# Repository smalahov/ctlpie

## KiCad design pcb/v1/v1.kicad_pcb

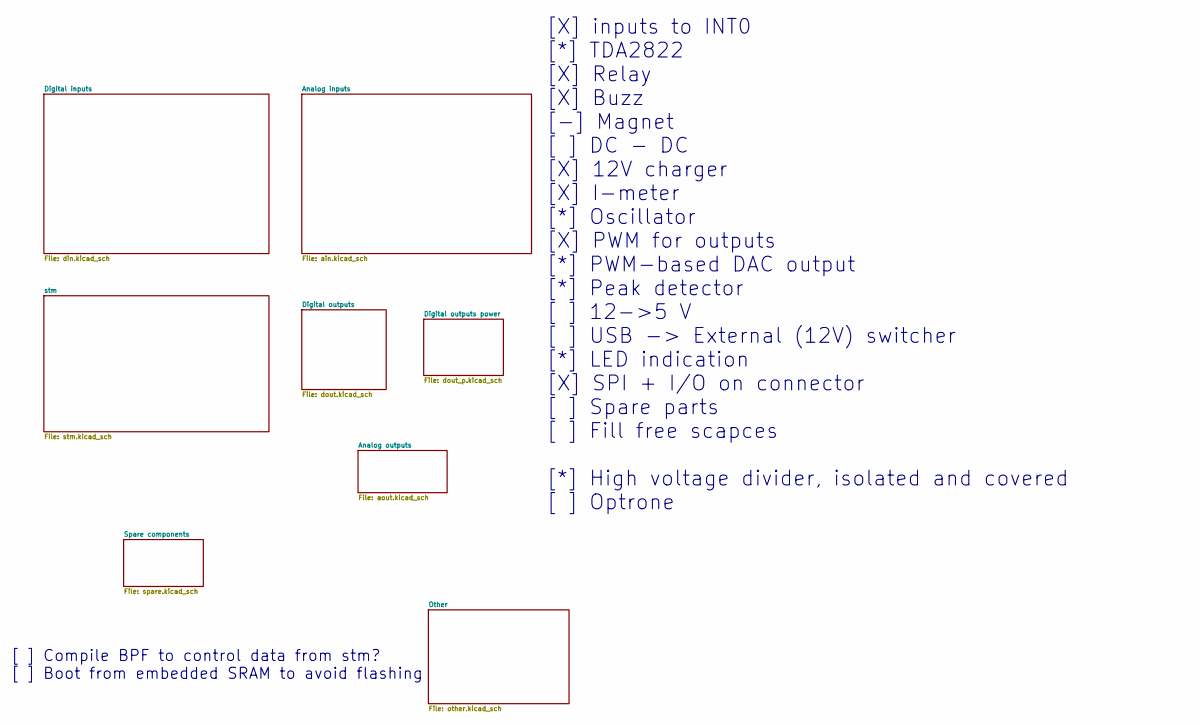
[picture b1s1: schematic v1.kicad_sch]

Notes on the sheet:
[X] inputs to INT0 [*] TDA2822 [X] Relay [X] Buzz [-] Magnet [ ] DC - DC [X] 12V charger [X] I-meter [*] Oscillator [X] PWM for outputs [*] PWM-based DAC output [*] Peak detector [ ] 12->5 V [ ] USB -> External (12V) switcher [*] LED indication [X] SPI + I/O on connector [ ] Spare parts [ ] Fill fr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
[ ] Compile BPF to control data from stm? [ ] Boot from embedded SRAM to avoid flashing

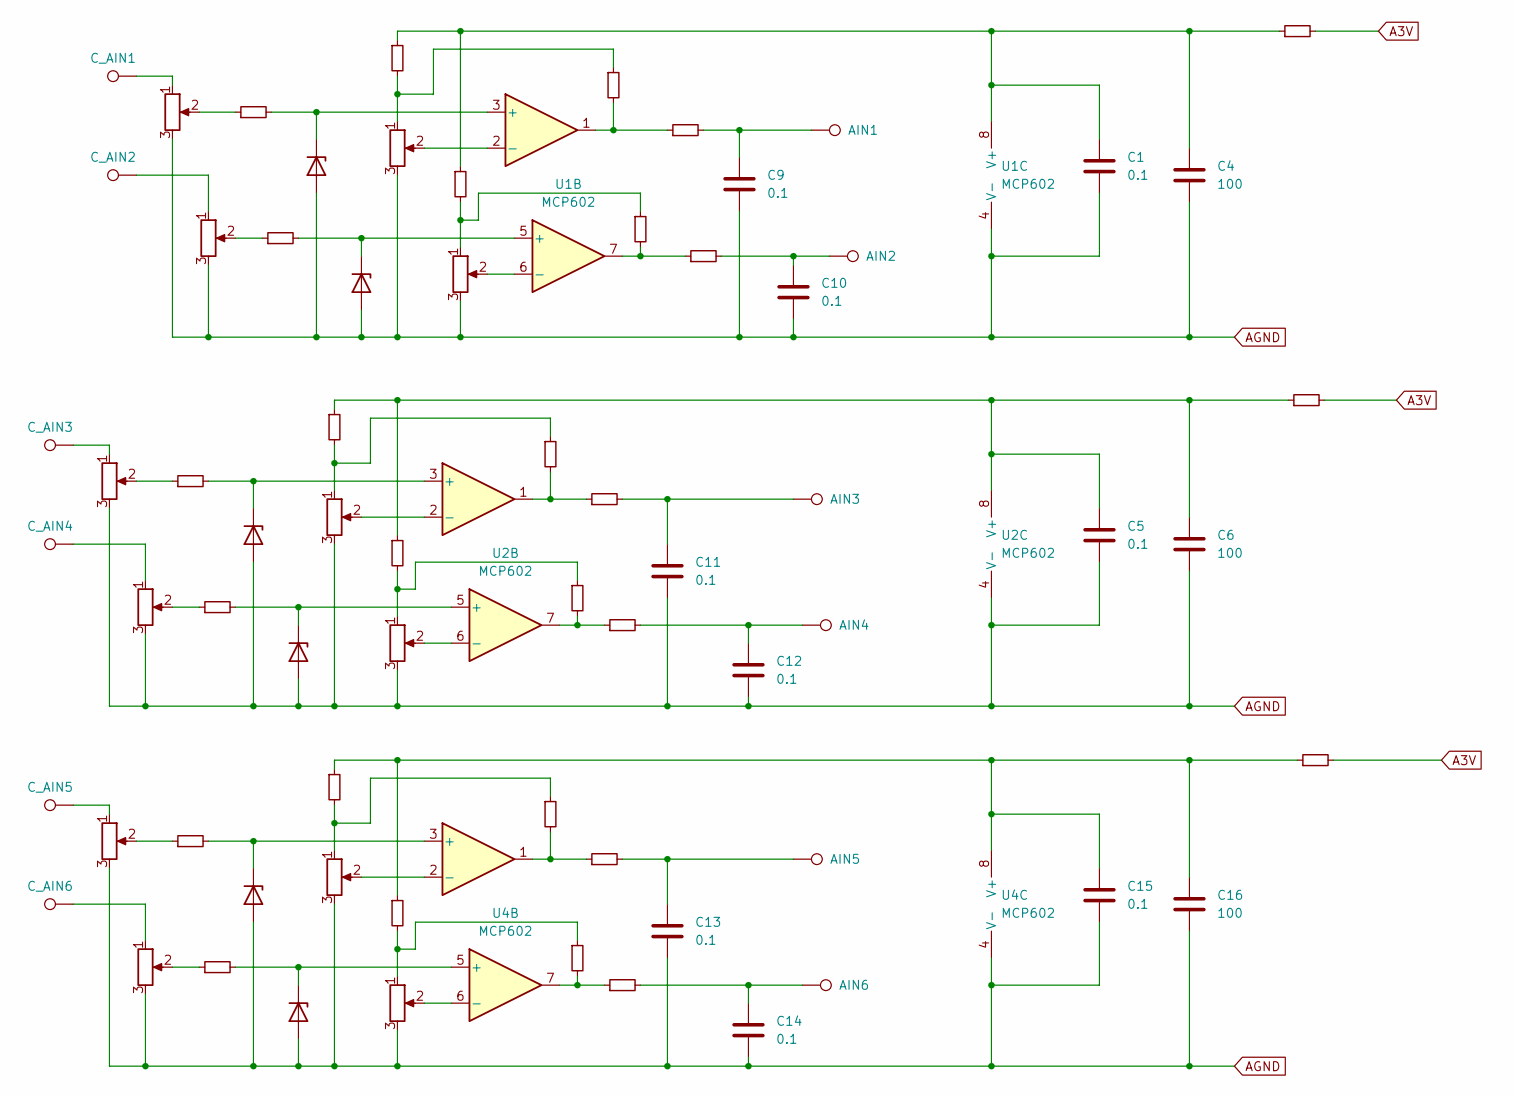
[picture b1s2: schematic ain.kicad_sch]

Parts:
AIN1, AIN2, AIN3, AIN4, AIN5, AIN6: TestPoint; TestPoint_Pad_2.0x2.0mm
C1, C5, C9, C10, C11, C12, C13, C14, C15: 0.1; C_1206_3216Metric
C4, C6, C16: 100; C_1206_3216Metric
C_AIN1, C_AIN2, C_AIN3, C_AIN4, C_AIN5, C_AIN6: TestPoint; TestPoint_Pad_D2.0mm
D2, D3, D9, D10, D11, D12: D_Zener; D_SOD-123
J1, J2, J3, J4, J5, J6, J7, J8, J9, J10, J11, J12, J13, J14, J15, J16, J18, J19, J20: R_Small; R_1206_3216Metric_Pad1.30x1.75mm_HandSolder
R5, R6, R50, R51, R52, R53, R200, R201: R_Small; R_1206_3216Metric_Pad1.30x1.75mm_HandSolder
RV1, RV2, RV3, RV4, RV5, RV6, RV7, RV8, RV9, RV10, RV14, RV15: R_Potentiometer; Potentiometer_Bourns_TC33X_Vertical
U1, U2, U4: MCP602; SOIC-8_3.9x4.9mm_P1.27mm

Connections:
A3V: J18.2, J19.2, J20.2; also elsewhere on the board
AGND: C1.2, C4.2, C5.2, C6.2, C9.2, C10.2, C11.2, C12.2, C13.2, C14.2, C15.2, C16.2, D2.2 (A), D3.2 (A), D9.2 (A), D10.2 (A), D11.2 (A), D12.2 (A), RV1.3, RV2.3, RV3.3, RV4.3, RV5.3, RV6.3, RV7.3, RV8.3, RV9.3, RV10.3, RV14.3, RV15.3, U1.4 (V-), U2.4 (V-), U4.4 (V-); also elsewhere on the board
unnamed 8: AIN1.1, C9.1, R200.2; also elsewhere on the board
unnamed 9: AIN2.1, C10.1, R201.2; also elsewhere on the board
unnamed 10: AIN3.1, C11.1, J9.2; also elsewhere on the board
unnamed 11: AIN4.1, C12.1, J10.2; also elsewhere on the board
unnamed 12: AIN5.1, C13.1, J15.2; also elsewhere on the board
unnamed 13: AIN6.1, C14.1, J16.2; also elsewhere on the board
unnamed: C_AIN1.1, RV1.1
unnamed: C_AIN2.1, RV5.1
unnamed: C_AIN3.1, RV3.1
unnamed: C_AIN4.1, RV7.1
unnamed: C_AIN5.1, RV9.1
unnamed: C_AIN6.1, RV10.1
unnamed: D2.1 (K), R5.2, U1.3 (+)
unnamed: D3.1 (K), R6.2, U1.5 (+)
unnamed: D9.1 (K), R50.2, U2.3 (+)
unnamed: D10.1 (K), R51.2, U2.5 (+)
unnamed: D11.1 (K), R52.2, U4.3 (+)
unnamed: D12.1 (K), R53.2, U4.5 (+)
unnamed: J1.2, J2.1, RV2.1
unnamed: J2.2, R200.1, U1.1
unnamed: J3.2, J4.1, RV6.1
unnamed: J4.2, R201.1, U1.7
unnamed: J5.2, J7.1, RV4.1
unnamed: J6.2, J8.1, RV8.1
unnamed: J7.2, J9.1, U2.1
unnamed: J8.2, J10.1, U2.7
unnamed: J11.2, J13.1, RV14.1
unnamed: J12.2, J14.1, RV15.1
unnamed: J13.2, J15.1, U4.1
unnamed: J14.2, J16.1, U4.7
unnamed: R5.1, RV1.2
unnamed: R6.1, RV5.2
unnamed: R50.1, RV3.2
unnamed: R51.1, RV7.2
unnamed: R52.1, RV9.2
unnamed: R53.1, RV10.2
unnamed: RV2.2, U1.2 (-)
unnamed: RV6.2, U1.6 (-)
unnamed: C1.1, C4.1, J1.1, J3.1, J18.1, U1.8 (V+)
unnamed: RV4.2, U2.2 (-)
unnamed: RV8.2, U2.6 (-)
unnamed: C5.1, C6.1, J5.1, J6.1, J19.1, U2.8 (V+)
unnamed: RV14.2, U4.2 (-)
unnamed: RV15.2, U4.6 (-)
unnamed: C15.1, C16.1, J11.1, J12.1, J20.1, U4.8 (V+)

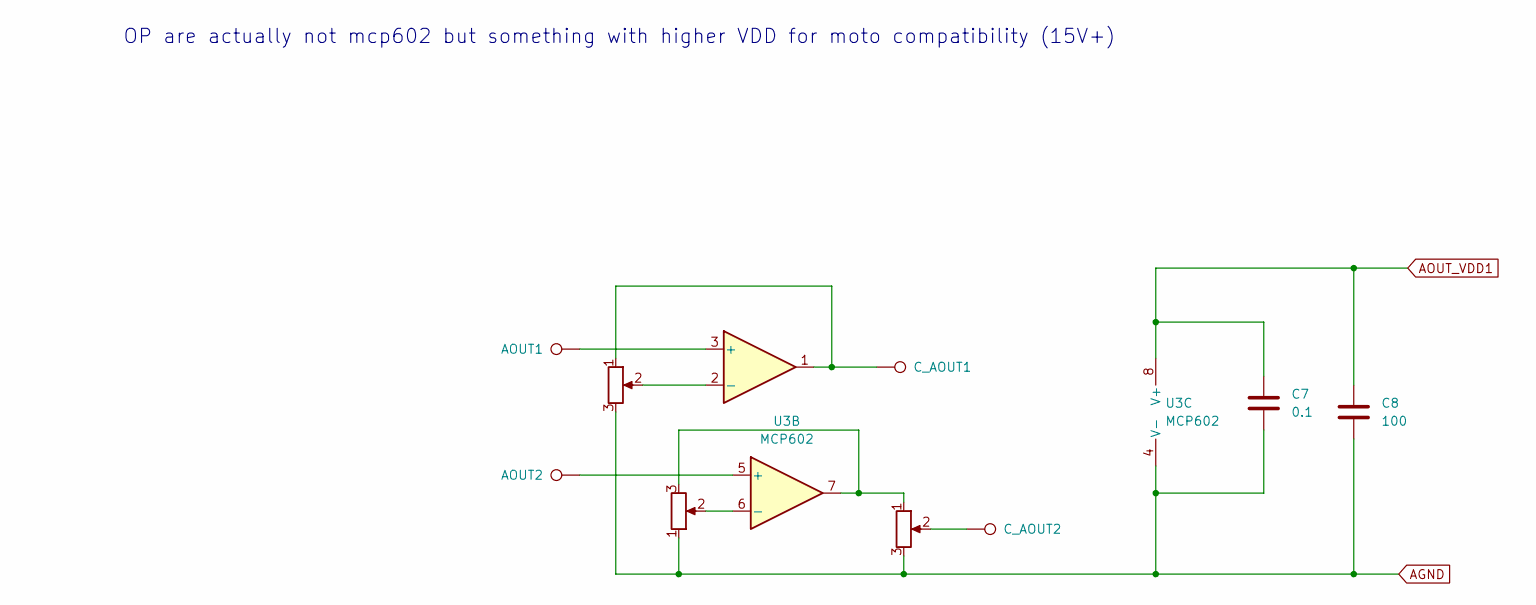
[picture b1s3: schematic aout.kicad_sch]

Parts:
AOUT1, AOUT2: TestPoint; TestPoint_Pad_2.0x2.0mm
C7: 0.1; C_1206_3216Metric
C8: 100; C_1206_3216Metric
C_AOUT1, C_AOUT2: TestPoint; TestPoint_Pad_D2.0mm
RV11, RV12, RV13: R_Potentiometer; Potentiometer_Bourns_TC33X_Vertical
U3: MCP602; SOIC-8_3.9x4.9mm_P1.27mm

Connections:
AGND: C7.2, C8.2, RV11.3, RV12.1, RV13.3, U3.4 (V-); also elsewhere on the board
AOUT_VDD1: C7.1, C8.1, U3.8 (V+)
unnamed: C_AOUT1.1, RV11.1, U3.1
unnamed: C_AOUT2.1, RV13.2
unnamed: RV12.3, RV13.1, U3.7
unnamed: AOUT1.1, U3.3 (+)
unnamed: RV11.2, U3.2 (-)
unnamed: AOUT2.1, U3.5 (+)
unnamed: RV12.2, U3.6 (-)

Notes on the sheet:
OP are actually not mcp602 but something with higher VDD for moto compatibility (15V+)

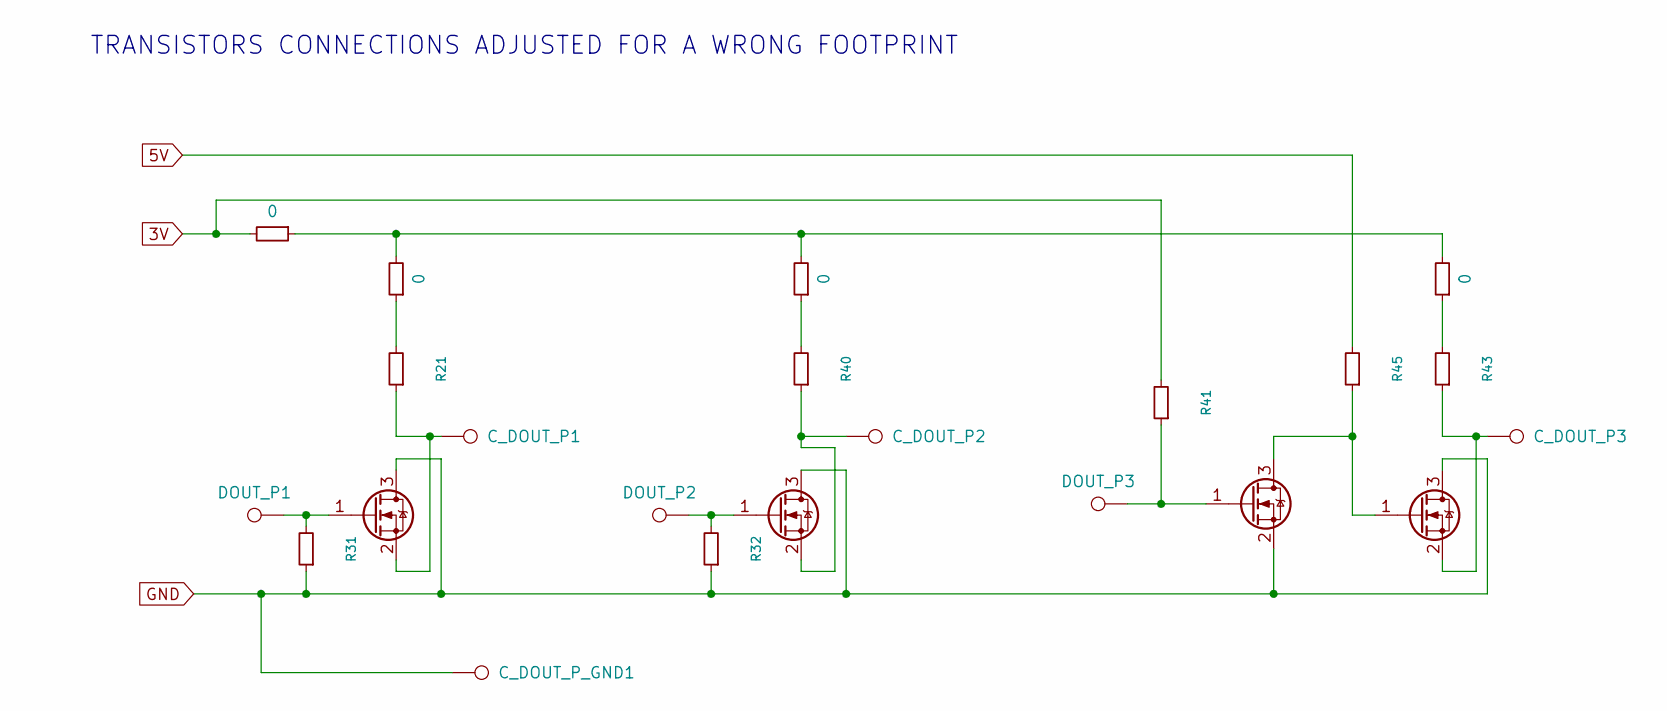
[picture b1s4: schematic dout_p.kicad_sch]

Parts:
C_DOUT_P1, C_DOUT_P2, C_DOUT_P3: TestPoint; TestPoint_Pad_D2.0mm
C_DOUT_P_GND1: TestPoint; TestPoint_Pad_D2.0mm
DOUT_P1, DOUT_P2, DOUT_P3: TestPoint; TestPoint_Pad_2.0x2.0mm
Q6, Q12, Q13: 35N06; TO-252-2
Q14: 2N7002K; SOT-23-3
R21, R31, R32, R40, R41, R43, R45: R_Small; R_1206_3216Metric_Pad1.30x1.75mm_HandSolder
R22, R37, R42, R44: 0; R_1206_3216Metric_Pad1.30x1.75mm_HandSolder

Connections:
3V: R41.2, R44.2; also elsewhere on the board
5V: R45.2; also elsewhere on the board
GND: C_DOUT_P_GND1.1, Q6.3 (D), Q12.3 (D), Q13.3 (D), Q14.2 (S), R31.1, R32.1; also elsewhere on the board
unnamed: DOUT_P1.1, Q6.1 (G), R31.2
unnamed: C_DOUT_P1.1, Q6.2 (S), R21.1
unnamed: DOUT_P2.1, Q12.1 (G), R32.2
unnamed: C_DOUT_P2.1, Q12.2 (S), R40.1
unnamed: Q13.1 (G), Q14.3 (D), R45.1
unnamed: C_DOUT_P3.1, Q13.2 (S), R43.1
unnamed: DOUT_P3.1, Q14.1 (G), R41.1
unnamed: R21.2, R22.1
unnamed: R22.2, R37.2, R42.2, R44.1
unnamed: R37.1, R40.2
unnamed: R42.1, R43.2

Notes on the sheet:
TRANSISTORS CONNECTIONS ADJUSTED FOR A WRONG FOOTPRINT

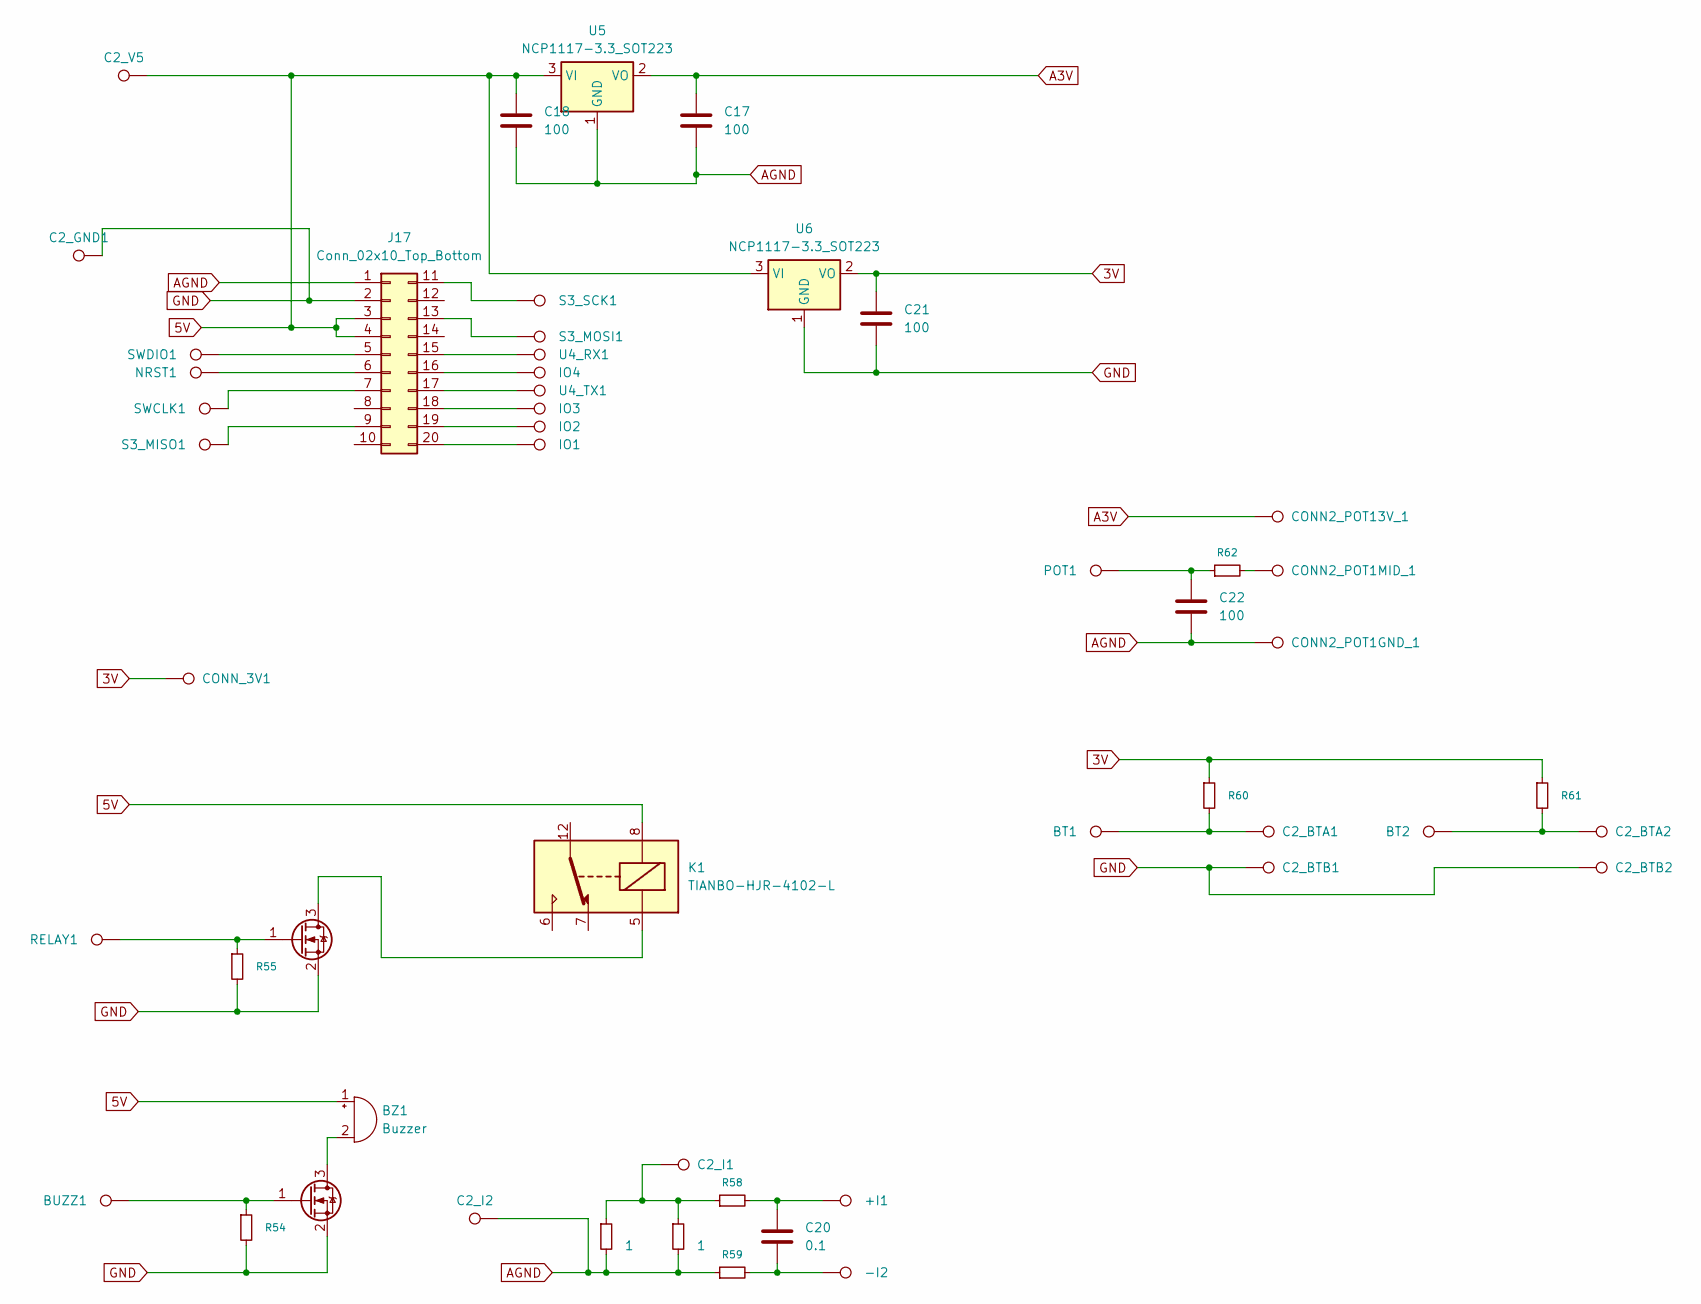
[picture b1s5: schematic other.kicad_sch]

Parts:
+I1: TestPoint; TestPoint_Pad_2.0x2.0mm
-I2: TestPoint; TestPoint_Pad_2.0x2.0mm
BT1, BT2: TestPoint; TestPoint_Pad_2.0x2.0mm
BUZZ1: TestPoint; TestPoint_Pad_2.0x2.0mm
BZ1: Buzzer; Indicator_PUI_AI-1440-TWT-24V-2-R
C2_BTA1, C2_BTA2, C2_BTB1, C2_BTB2, C2_GND1, C2_I1, C2_I2, C2_V5: TestPoint; TestPoint_Pad_D2.0mm
C17, C18, C21, C22: 100; C_1206_3216Metric
C20: 0.1; C_1206_3216Metric
CONN2_POT1GND_1, CONN2_POT1MID_1, CONN2_POT13V_1: TestPoint; TestPoint_Pad_D2.0mm
CONN_3V1: TestPoint; TestPoint_Pad_D2.0mm
IO1, IO2, IO3, IO4: TestPoint; TestPoint_Pad_2.0x2.0mm
J17: Conn_02x10_Top_Bottom; IDC-Header_2x10_P2.54mm_Vertical
K1: TIANBO-HJR-4102-L; Relay_SPDT_HJR-4102
NRST1: TestPoint; TestPoint_Pad_2.0x2.0mm
POT1: TestPoint; TestPoint_Pad_2.0x2.0mm
Q17, Q18: 2N7002K; SOT-23-3
R54, R55, R58, R59, R60, R61, R62: R_Small; R_1206_3216Metric_Pad1.30x1.75mm_HandSolder
R56, R57: 1; R_2512_6332Metric_Pad1.40x3.35mm_HandSolder
RELAY1: TestPoint; TestPoint_Pad_2.0x2.0mm
S3_MISO1, S3_MOSI1, S3_SCK1: TestPoint; TestPoint_Pad_2.0x2.0mm
SWCLK1: TestPoint; TestPoint_Pad_2.0x2.0mm
SWDIO1: TestPoint; TestPoint_Pad_2.0x2.0mm
U4_RX1, U4_TX1: TestPoint; TestPoint_Pad_2.0x2.0mm
U5, U6: NCP1117-3.3_SOT223; SOT-223-3_TabPin2

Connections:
3V: C21.1, CONN_3V1.1, R60.1, R61.1, U6.2 (VO); also elsewhere on the board
5V: BZ1.1 (+), C2_V5.1, C18.1, J17.3, J17.4, K1.8, U5.3 (VI), U6.3 (VI); also elsewhere on the board
A3V: C17.1, CONN2_POT13V_1.1, U5.2 (VO); also elsewhere on the board
AGND: C2_I2.1, C17.2, C18.2, C22.2, CONN2_POT1GND_1.1, J17.1, R56.2, R57.2, R59.1, U5.1 (GND); also elsewhere on the board
GND: C2_BTB1.1, C2_BTB2.1, C2_GND1.1, C21.2, J17.2, Q17.2 (S), Q18.2 (S), R54.2, R55.2, U6.1 (GND); also elsewhere on the board
unnamed 6: +I1.1, C20.1, R58.2; also elsewhere on the board
unnamed 7: -I2.1, C20.2, R59.2; also elsewhere on the board
unnamed: BT1.1, C2_BTA1.1, R60.2
unnamed: BT2.1, C2_BTA2.1, R61.2
unnamed: BZ1.2 (-), Q17.3 (D)
unnamed: C2_I1.1, R56.1, R57.1, R58.1
unnamed 18: C22.1, POT1.1, R62.1; also elsewhere on the board
unnamed: CONN2_POT1MID_1.1, R62.2
unnamed: J17.5, SWDIO1.1
unnamed 75: J17.6, NRST1.1; also elsewhere on the board
unnamed: J17.7, SWCLK1.1
unnamed: J17.9, S3_MISO1.1
unnamed: J17.11, S3_SCK1.1
unnamed: J17.13, S3_MOSI1.1
unnamed: J17.15, U4_RX1.1
unnamed: IO4.1, J17.16
unnamed: J17.17, U4_TX1.1
unnamed: IO3.1, J17.18
unnamed: IO2.1, J17.19
unnamed: IO1.1, J17.20
unnamed: BUZZ1.1, Q17.1 (G), R54.1
unnamed: K1.5, Q18.3 (D)
unnamed: Q18.1 (G), R55.1, RELAY1.1

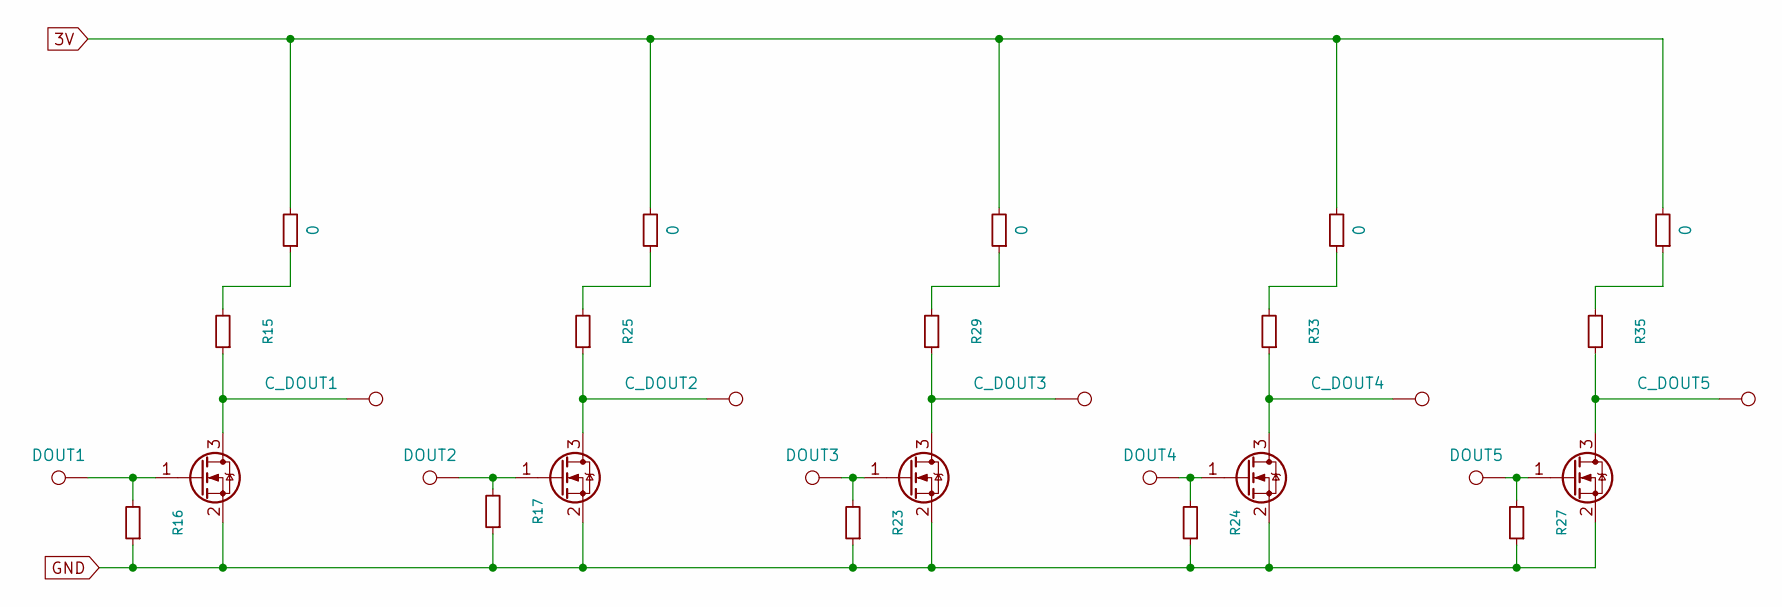
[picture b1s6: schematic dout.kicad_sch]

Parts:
C_DOUT1, C_DOUT2, C_DOUT3, C_DOUT4, C_DOUT5: TestPoint; TestPoint_Pad_D2.0mm
DOUT1, DOUT2, DOUT3, DOUT4, DOUT5: TestPoint; TestPoint_Pad_2.0x2.0mm
Q5, Q7, Q8, Q9, Q10: 2N7002K; SOT-23-3
R15, R16, R17, R23, R24, R25, R27, R29, R33, R35: R_Small; R_1206_3216Metric_Pad1.30x1.75mm_HandSolder
R18, R26, R30, R34, R36: 0; R_1206_3216Metric_Pad1.30x1.75mm_HandSolder

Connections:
3V: R18.2, R26.2, R30.2, R34.2, R36.2; also elsewhere on the board
GND: Q5.2 (S), Q7.2 (S), Q8.2 (S), Q9.2 (S), Q10.2 (S), R16.1, R17.1, R23.1, R24.1, R27.1; also elsewhere on the board
unnamed: C_DOUT1.1, Q5.3 (D), R15.1
unnamed: DOUT1.1, Q5.1 (G), R16.2
unnamed: C_DOUT2.1, Q7.3 (D), R25.1
unnamed: DOUT2.1, Q7.1 (G), R17.2
unnamed: C_DOUT3.1, Q8.3 (D), R29.1
unnamed: DOUT3.1, Q8.1 (G), R23.2
unnamed: C_DOUT4.1, Q9.3 (D), R33.1
unnamed: DOUT4.1, Q9.1 (G), R24.2
unnamed: C_DOUT5.1, Q10.3 (D), R35.1
unnamed: DOUT5.1, Q10.1 (G), R27.2
unnamed: R15.2, R18.1
unnamed: R25.2, R26.1
unnamed: R29.2, R30.1
unnamed: R33.2, R34.1
unnamed: R35.2, R36.1

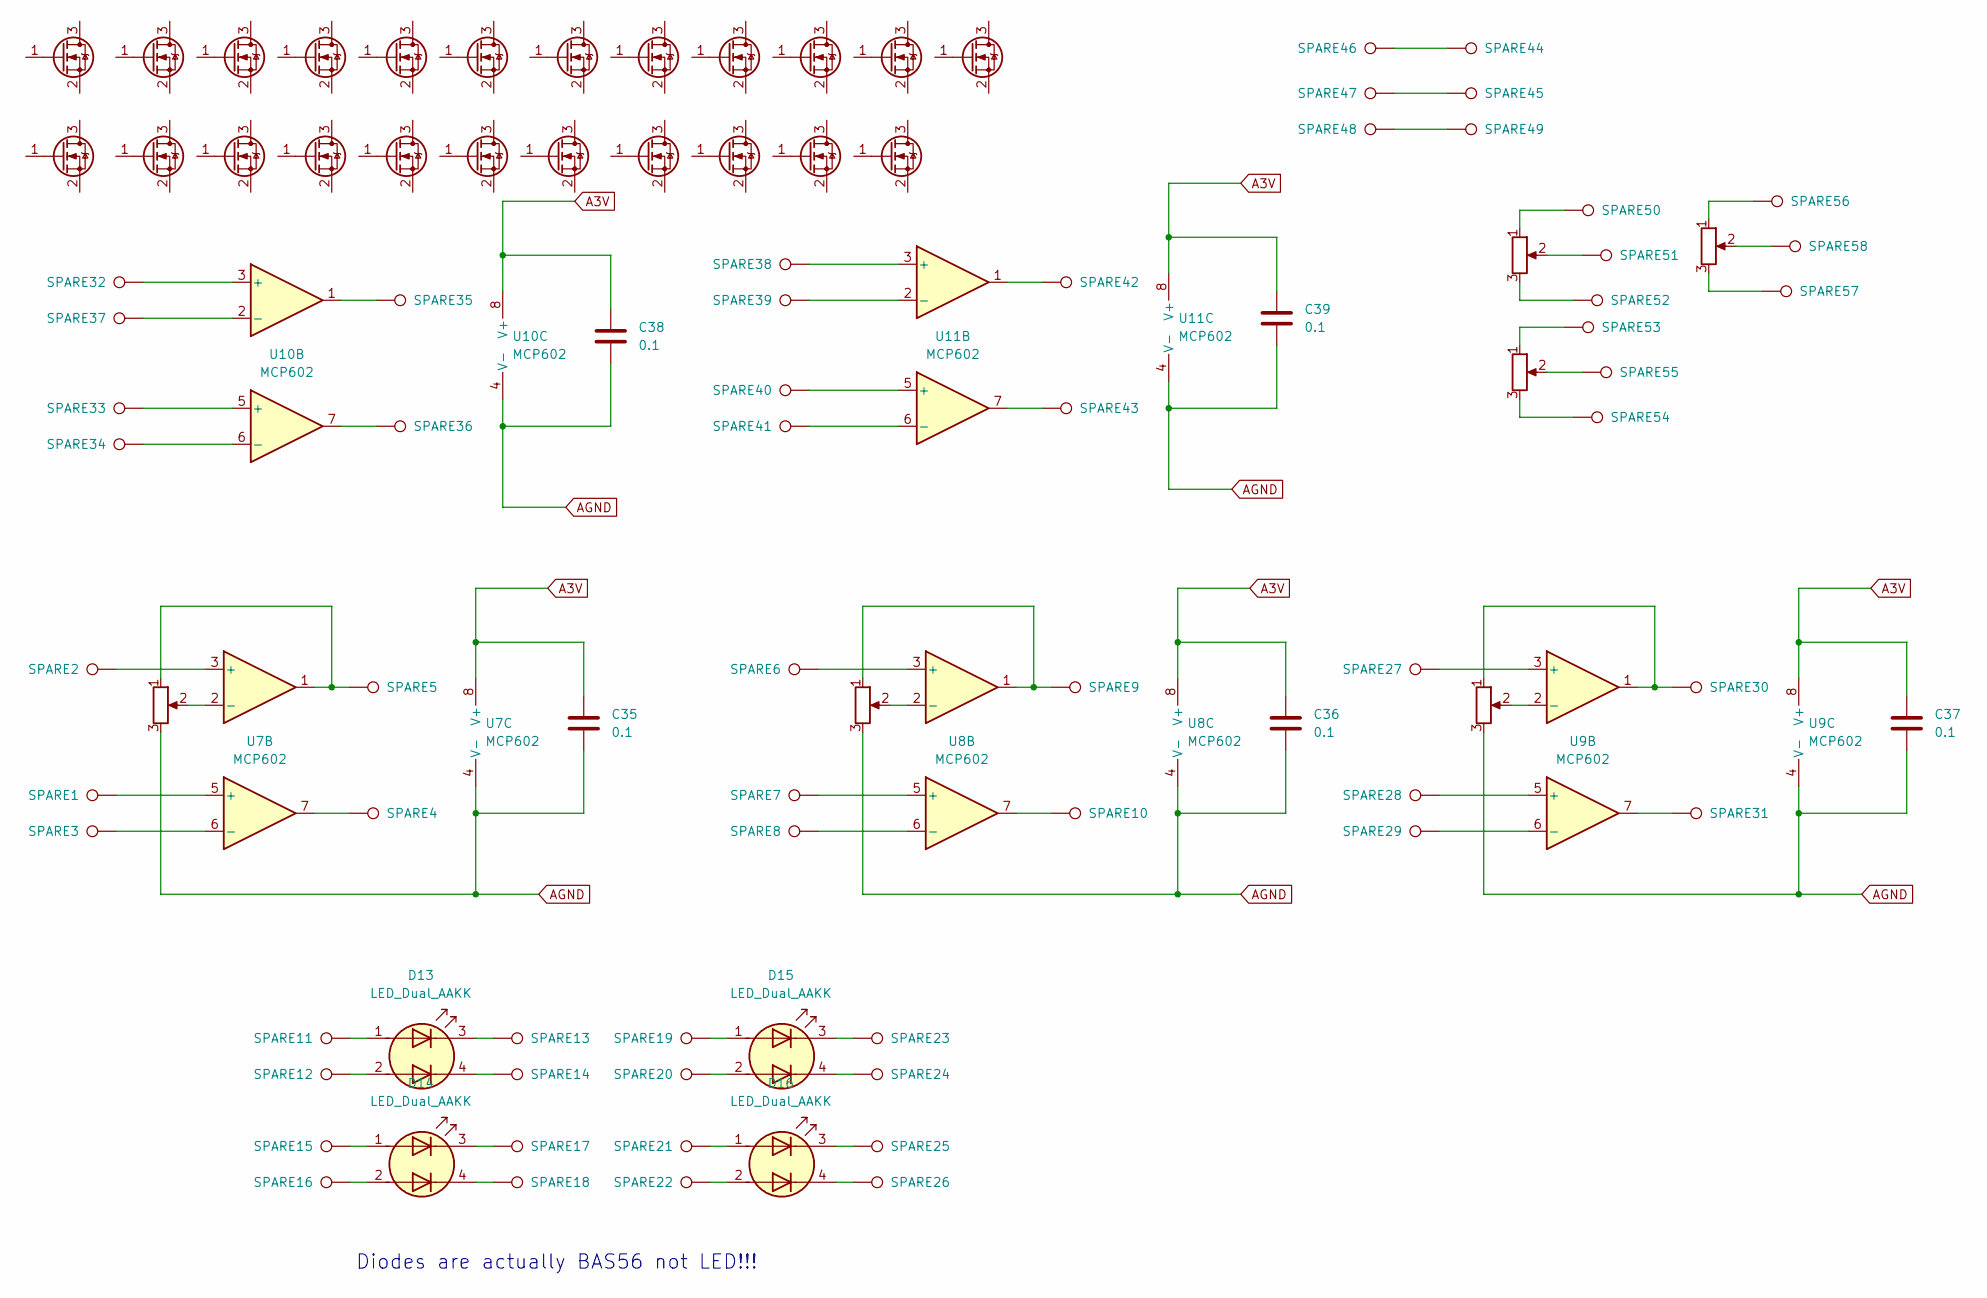
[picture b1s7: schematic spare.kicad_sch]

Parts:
C35, C36, C37, C38, C39: 0.1; C_1206_3216Metric
D13, D14, D15, D16: LED_Dual_AAKK; SOT-143
Q11, Q19, Q20, Q21, Q22, Q23, Q24, Q25, Q26, Q27, Q28, Q29, Q30, Q31, Q32, Q33, Q34, Q35, Q36, Q37, Q38, Q39, Q40: 2N7002K; SOT-23_Handsoldering
RV16, RV17, RV18, RV19, RV20, RV21: R_Potentiometer; Potentiometer_Bourns_TC33X_Vertical
SPARE1, SPARE2, SPARE3, SPARE4, SPARE5, SPARE6, SPARE7, SPARE8, SPARE9, SPARE10, SPARE11, SPARE12, SPARE13, SPARE14, SPARE15, SPARE16, SPARE17, SPARE18, SPARE19, SPARE20, SPARE21, SPARE22, SPARE23, SPARE24, SPARE25, SPARE26, SPARE27, SPARE28, SPARE29, SPARE30, SPARE31, SPARE32, SPARE33, SPARE34, SPARE35, SPARE36, SPARE37, SPARE38, SPARE39, SPARE40, SPARE41, SPARE42, SPARE43: TestPoint; TestPoint_Pad_1.0x1.0mm
SPARE44, SPARE45, SPARE49: TestPoint; TestPoint_Pad_D2.0mm
SPARE46, SPARE47, SPARE48: TestPoint; TestPoint_Pad_2.0x2.0mm
SPARE50, SPARE51, SPARE52, SPARE53, SPARE54, SPARE55, SPARE56, SPARE57, SPARE58: TestPoint; TestPoint_Pad_1.5x1.5mm
U7, U8, U9, U10, U11: MCP602; SOIC-8_3.9x4.9mm_P1.27mm

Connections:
A3V: C35.1, C36.1, C37.1, C38.1, C39.1, U7.8 (V+), U8.8 (V+), U9.8 (V+), U10.8 (V+), U11.8 (V+); also elsewhere on the board
AGND: C35.2, C36.2, C37.2, C38.2, C39.2, RV16.3, RV17.3, RV18.3, U7.4 (V-), U8.4 (V-), U9.4 (V-), U10.4 (V-), U11.4 (V-); also elsewhere on the board
unnamed: D13.1 (A1), SPARE11.1
unnamed: D13.2 (A2), SPARE12.1
unnamed: D13.3 (K1), SPARE13.1
unnamed: D13.4 (K2), SPARE14.1
unnamed: D14.1 (A1), SPARE15.1
unnamed: D14.2 (A2), SPARE16.1
unnamed: D14.3 (K1), SPARE17.1
unnamed: D14.4 (K2), SPARE18.1
unnamed: D15.1 (A1), SPARE19.1
unnamed: D15.2 (A2), SPARE20.1
unnamed: D15.3 (K1), SPARE23.1
unnamed: D15.4 (K2), SPARE24.1
unnamed: D16.1 (A1), SPARE21.1
unnamed: D16.2 (A2), SPARE22.1
unnamed: D16.3 (K1), SPARE25.1
unnamed: D16.4 (K2), SPARE26.1
unnamed: RV16.1, SPARE5.1, U7.1
unnamed: RV17.1, SPARE9.1, U8.1
unnamed: RV18.1, SPARE30.1, U9.1
unnamed: RV19.1, SPARE50.1
unnamed: RV19.2, SPARE51.1
unnamed: RV19.3, SPARE52.1
unnamed: RV20.1, SPARE53.1
unnamed: RV20.2, SPARE55.1
unnamed: RV20.3, SPARE54.1
unnamed: RV21.1, SPARE56.1
unnamed: RV21.2, SPARE58.1
unnamed: RV21.3, SPARE57.1
unnamed: SPARE4.1, U7.7
unnamed: SPARE10.1, U8.7
unnamed: SPARE31.1, U9.7
unnamed: SPARE35.1, U10.1
unnamed: SPARE36.1, U10.7
unnamed: SPARE42.1, U11.1
unnamed: SPARE43.1, U11.7
unnamed: SPARE44.1, SPARE46.1
unnamed: SPARE45.1, SPARE47.1
unnamed: SPARE48.1, SPARE49.1
unnamed: SPARE2.1, U7.3 (+)
unnamed: RV16.2, U7.2 (-)
unnamed: SPARE1.1, U7.5 (+)
unnamed: SPARE3.1, U7.6 (-)
unnamed: SPARE6.1, U8.3 (+)
unnamed: RV17.2, U8.2 (-)
unnamed: SPARE7.1, U8.5 (+)
unnamed: SPARE8.1, U8.6 (-)
unnamed: SPARE27.1, U9.3 (+)
unnamed: RV18.2, U9.2 (-)
unnamed: SPARE28.1, U9.5 (+)
unnamed: SPARE29.1, U9.6 (-)
unnamed: SPARE32.1, U10.3 (+)
unnamed: SPARE37.1, U10.2 (-)
unnamed: SPARE33.1, U10.5 (+)
unnamed: SPARE34.1, U10.6 (-)
unnamed: SPARE38.1, U11.3 (+)
unnamed: SPARE39.1, U11.2 (-)
unnamed: SPARE40.1, U11.5 (+)
unnamed: SPARE41.1, U11.6 (-)

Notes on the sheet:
Diodes are actually BAS56 not LED!!!

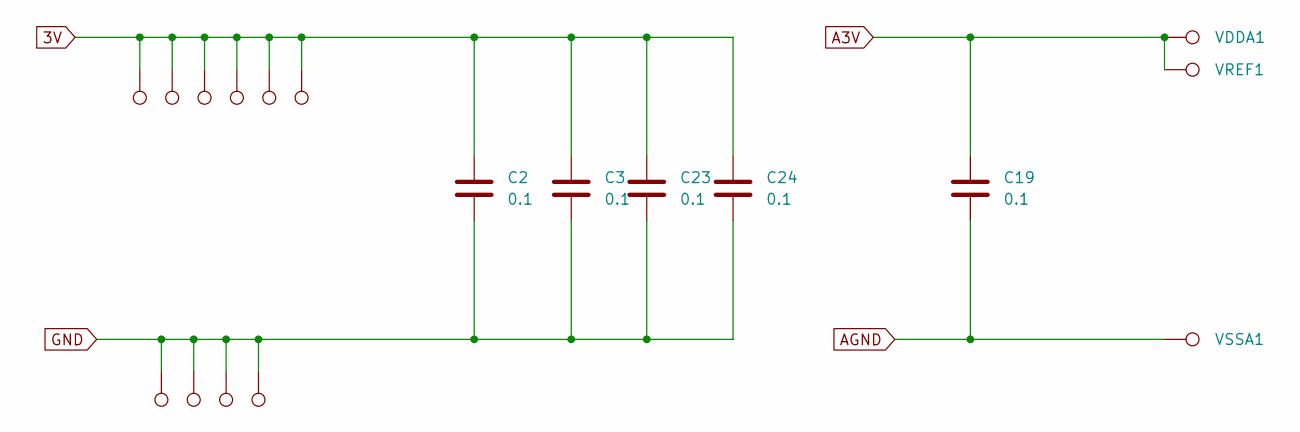
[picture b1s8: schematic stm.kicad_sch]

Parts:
C2, C3, C19, C23, C24: 0.1; C_1206_3216Metric
TP1, TP2, TP3, TP4, TP6, TP7, TP8, TP9, TP10, TP11: TestPoint; TestPoint_Pad_2.0x2.0mm
VDDA1: TestPoint; TestPoint_Pad_2.0x2.0mm
VREF1: TestPoint; TestPoint_Pad_2.0x2.0mm
VSSA1: TestPoint; TestPoint_Pad_2.0x2.0mm

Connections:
3V: C2.1, C3.1, C23.1, C24.1, TP6.1, TP7.1, TP8.1, TP9.1, TP10.1, TP11.1; also elsewhere on the board
A3V: C19.1, VDDA1.1, VREF1.1; also elsewhere on the board
AGND: C19.2, VSSA1.1; also elsewhere on the board
GND: C2.2, C3.2, C23.2, C24.2, TP1.1, TP2.1, TP3.1, TP4.1; also elsewhere on the board

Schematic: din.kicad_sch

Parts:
C_DIN1, C_DIN2, C_DIN3, C_DIN4, C_DIN5, C_DIN6: TestPoint; TestPoint_Pad_D2.0mm
D1, D4, D5, D6, D7, D8: D_Zener; D_SOD-123
DIN1, DIN2, DIN3, DIN4, DIN5, DIN6: TestPoint; TestPoint_Pad_2.0x2.0mm
Q1, Q2, Q3, Q4, Q15, Q16: 2N7002K; SOT-23-3
R1, R2, R3, R4, R7, R8, R9, R10, R11, R12, R13, R14, R19, R20, R46, R47, R48, R49: R_Small; R_1206_3216Metric_Pad1.30x1.75mm_HandSolder

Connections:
3V: R3.2, R8.2, R11.2, R14.2, R46.2, R49.2; also elsewhere on the board
GND: D1.2 (A), D4.2 (A), D5.2 (A), D6.2 (A), D7.2 (A), D8.2 (A), Q1.2 (S), Q2.2 (S), Q3.2 (S), Q4.2 (S), Q15.2 (S), Q16.2 (S), R1.2, R4.2, R9.2, R12.2, R19.2, R47.2; also elsewhere on the board
unnamed: C_DIN1.1, R1.1, R2.2
unnamed: C_DIN2.1, R4.1, R7.2
unnamed: C_DIN3.1, R9.1, R10.2
unnamed: C_DIN4.1, R12.1, R13.2
unnamed: C_DIN5.1, R19.1, R20.2
unnamed: C_DIN6.1, R47.1, R48.2
unnamed: D1.1 (K), Q1.1 (G), R2.1
unnamed: D4.1 (K), Q2.1 (G), R7.1
unnamed: D5.1 (K), Q3.1 (G), R10.1
unnamed: D6.1 (K), Q4.1 (G), R13.1
unnamed: D7.1 (K), Q15.1 (G), R20.1
unnamed: D8.1 (K), Q16.1 (G), R48.1
unnamed: DIN1.1, Q1.3 (D), R3.1
unnamed: DIN2.1, Q2.3 (D), R8.1
unnamed: DIN3.1, Q3.3 (D), R11.1
unnamed: DIN4.1, Q4.3 (D), R14.1
unnamed: DIN5.1, Q15.3 (D), R46.1
unnamed: DIN6.1, Q16.3 (D), R49.1

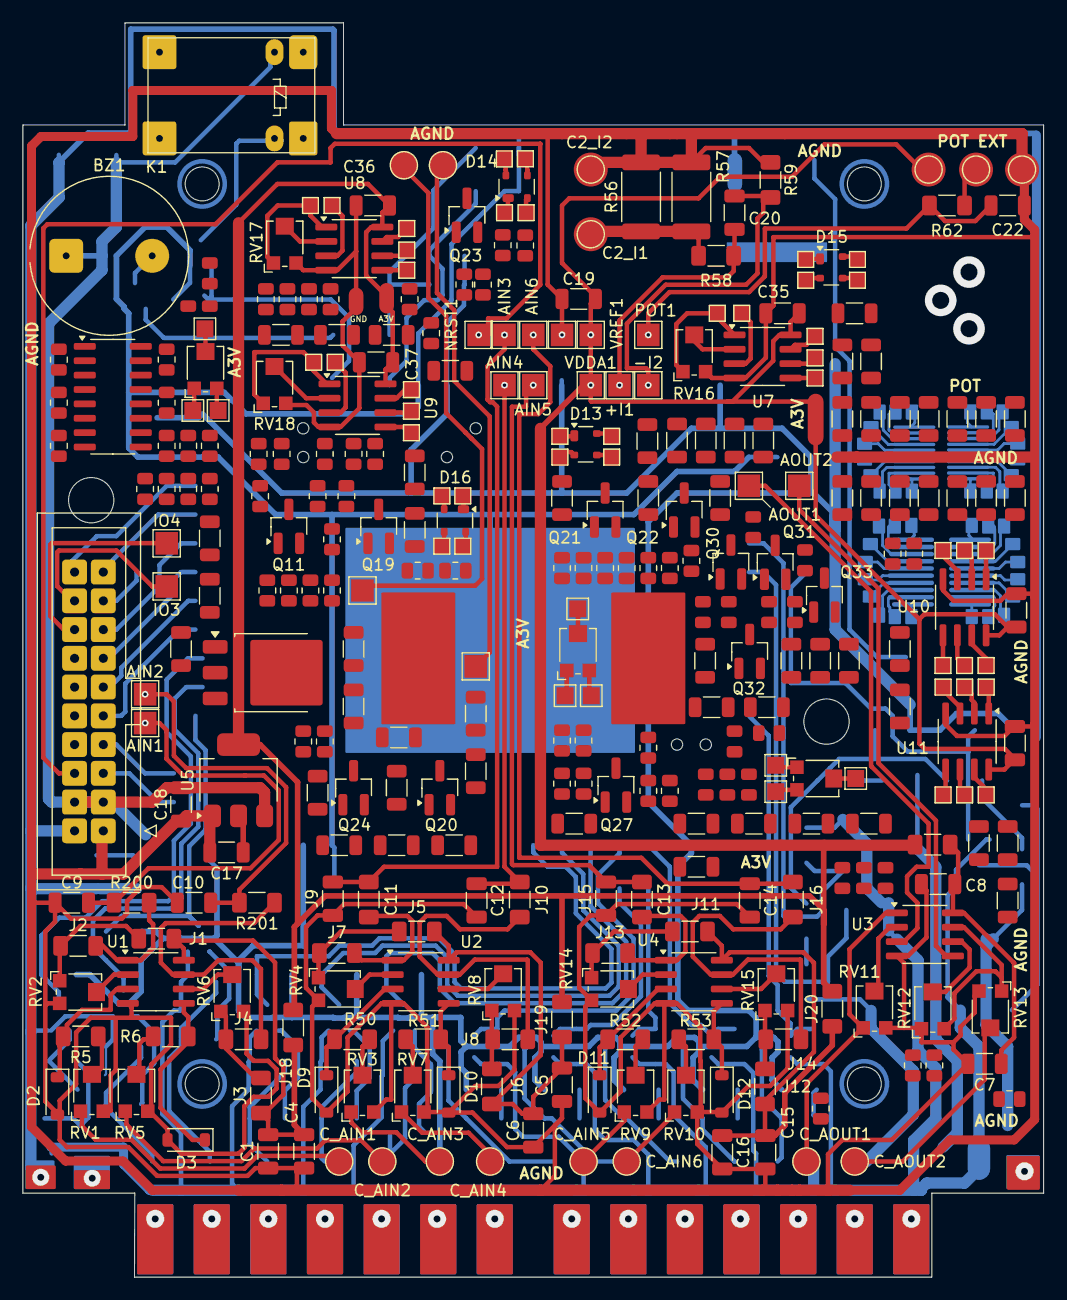
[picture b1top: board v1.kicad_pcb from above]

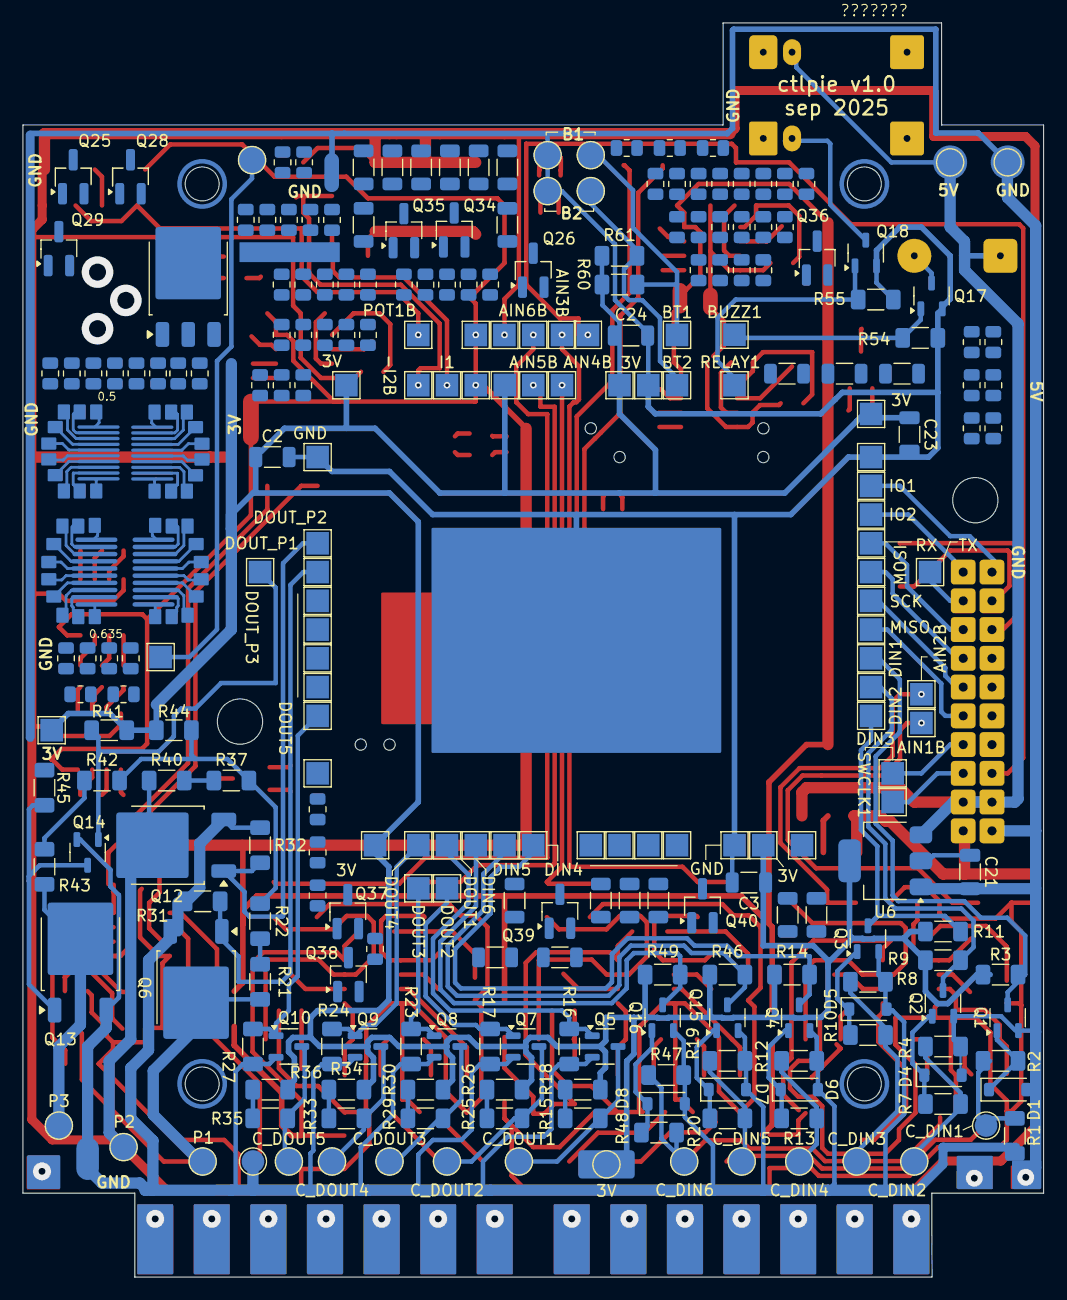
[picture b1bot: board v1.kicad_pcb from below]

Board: 2 copper layers, 90.2 x 110.8 mm, 360 parts (162 on the bottom side), 183 nets.

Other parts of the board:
-I2B: TestPoint; TestPoint_Pad_2.0x2.0mm
AIN1B, AIN2B, AIN3B, AIN4B, AIN5B, AIN6B: TestPoint; TestPoint_Pad_2.0x2.0mm
I1: TestPoint; TestPoint_Pad_2.0x2.0mm
NRST1B: TestPoint; TestPoint_Pad_2.0x2.0mm
POT1B: TestPoint; TestPoint_Pad_2.0x2.0mm
VDDA1B: TestPoint; TestPoint_Pad_2.0x2.0mm
VREF1B: TestPoint; TestPoint_Pad_2.0x2.0mm
VSSA1B: TestPoint; TestPoint_Pad_2.0x2.0mm

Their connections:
A3V: VDDA1B.1, VREF1B.1; also elsewhere on the board
AGND: VSSA1B.1; also elsewhere on the board
unnamed 6: I1.1; also elsewhere on the board
unnamed 7: -I2B.1; also elsewhere on the board
unnamed 8: AIN1B.1; also elsewhere on the board
unnamed 9: AIN2B.1; also elsewhere on the board
unnamed 10: AIN3B.1; also elsewhere on the board
unnamed 11: AIN4B.1; also elsewhere on the board
unnamed 12: AIN5B.1; also elsewhere on the board
unnamed 13: AIN6B.1; also elsewhere on the board
unnamed 18: POT1B.1; also elsewhere on the board
unnamed 75: NRST1B.1; also elsewhere on the board

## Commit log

2025-09-11 Initial commit: rough incomplete PCB design
2025-09-12 Added some spare unused parts and placeholders for future design
2025-09-17 Prepared for PCB ordering
2025-11-30 stm32/v1 firmware implementation
2025-12-11 Raspberry PI loggin service (v1)
